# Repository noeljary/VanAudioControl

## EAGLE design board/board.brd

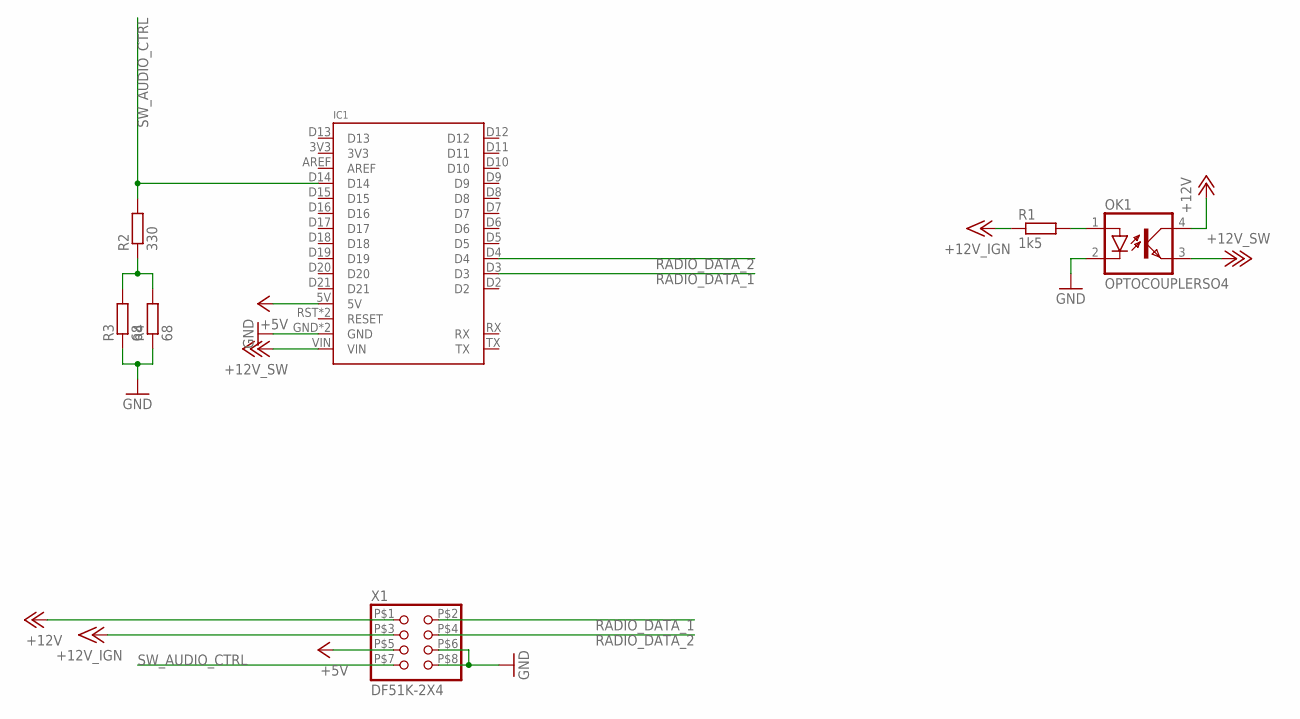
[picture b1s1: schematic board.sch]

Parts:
IC1: ARDUINO_NANO_EVERY
OK1: OPTOCOUPLERSO4; SO04
R1: 1k5; R0805
R2: 330; R0805
R3, R4: 68; R0805
X1: DF51K-2X4

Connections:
+5V: IC1.5V, X1.P$5 (5)
+12V: OK1.4 (COL), X1.P$1 (1)
+15V: R1.1, X1.P$3 (3)
+18V: IC1.VIN, OK1.3 (EMIT)
GND: IC1.GND, IC1.GND2 (GND), OK1.2 (C), R3.1, R4.1, X1.P$6 (6), X1.P$8 (8)
unnamed: OK1.1 (A), R1.2
unnamed: R2.1, R3.2, R4.2
RADIO_DATA_1: IC1.D3, X1.P$2 (2)
RADIO_DATA_2: IC1.D4, X1.P$4 (4)
SW_AUDIO_CTRL: IC1.D14, R2.2, X1.P$7 (7)

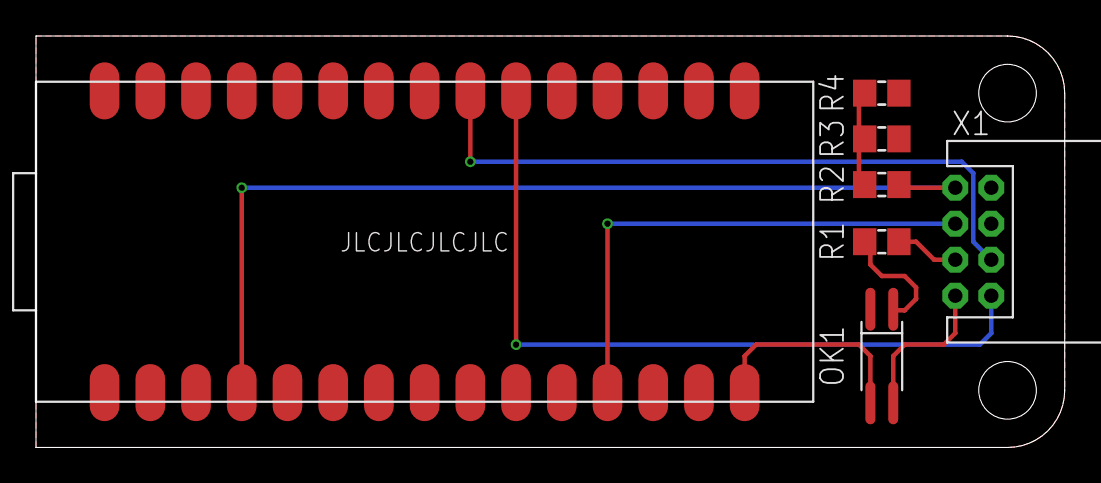
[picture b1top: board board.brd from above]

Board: 2 copper layers, 57.1 x 22.9 mm, 7 parts (0 on the bottom side), 10 nets.

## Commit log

2022-12-02 Initial commit for Steering Wheel Radio Controls
2023-04-29 Updated Button Press Sampling Algorithm due to Incorrect Button Detection, Seems some Hardware Issues Remain on Steering Wheel side
2023-04-29 Additional Debug Logging for Actual Sampled Resistance Value
2023-04-29 And some minor futher debug logging
